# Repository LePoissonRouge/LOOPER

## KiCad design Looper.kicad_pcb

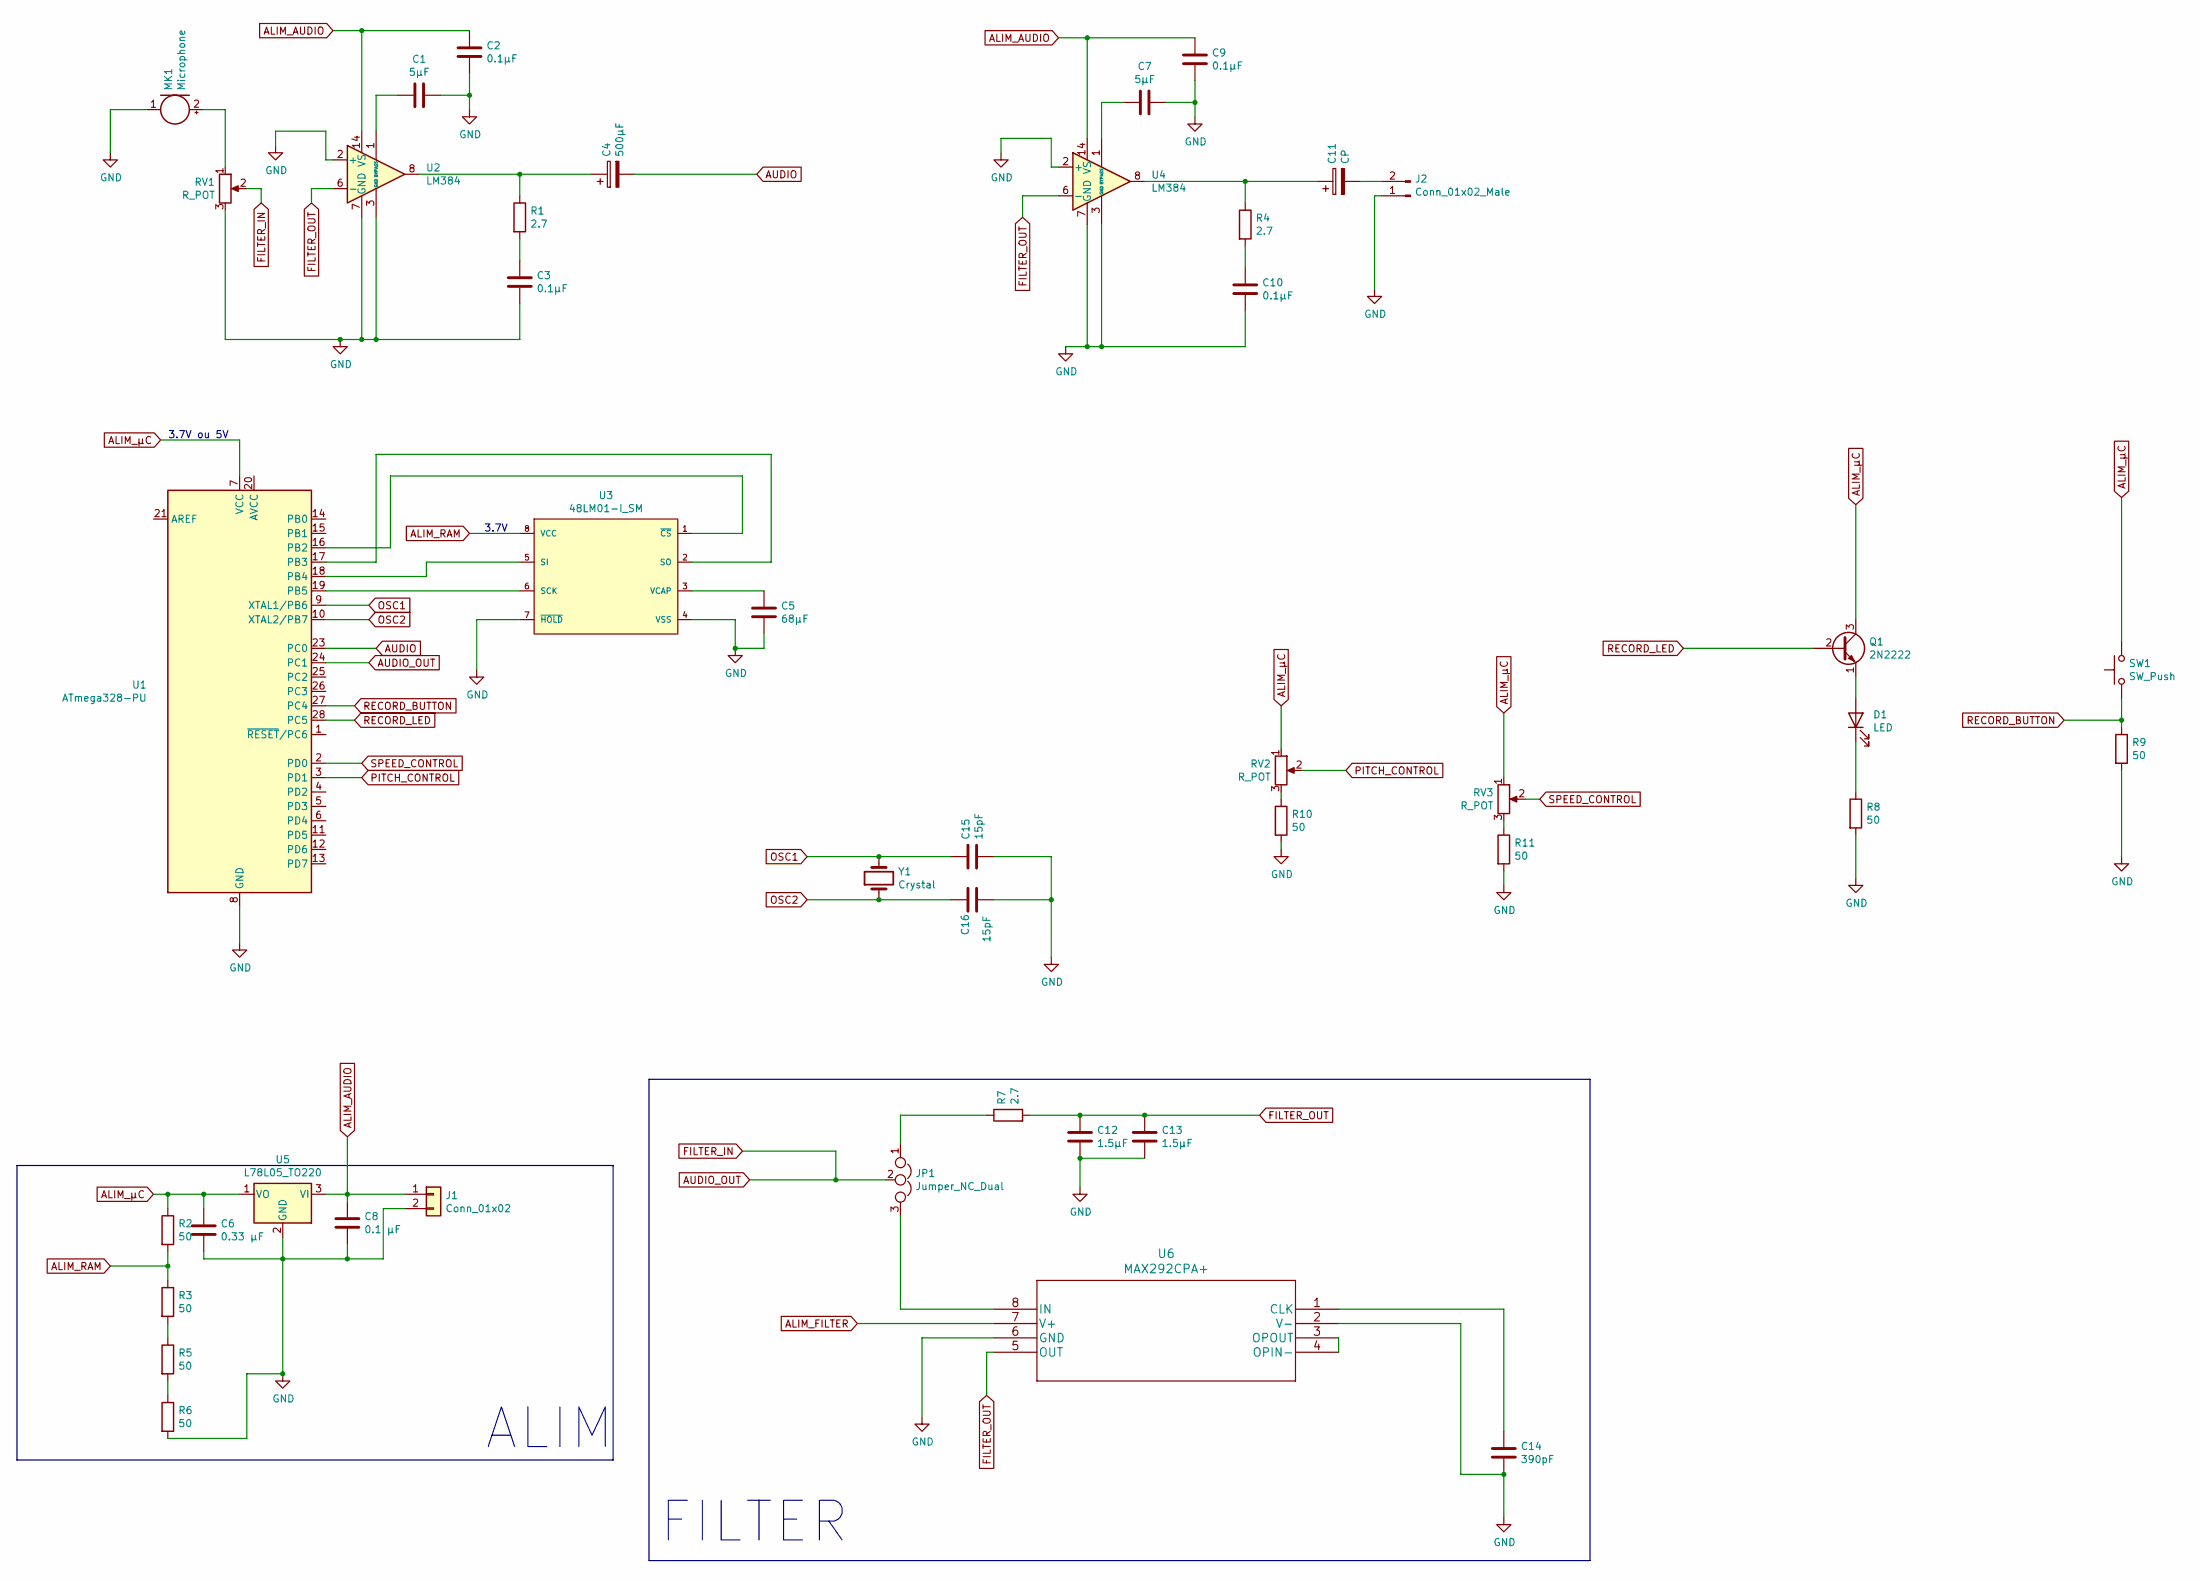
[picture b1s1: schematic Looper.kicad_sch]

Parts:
C1, C7: 5µF; C_Disc_D10.5mm_W5.0mm_P7.50mm
C2, C3, C9, C10: 0.1µF; C_Disc_D10.5mm_W5.0mm_P7.50mm
C4: 500µF; CP_Radial_D8.0mm_P3.50mm
C5: 68µF; C_1206_3216Metric_Pad1.33x1.80mm_HandSolder
C6: 0.33 µF; C_Disc_D10.5mm_W5.0mm_P7.50mm
C8: 0.1 µF; C_Disc_D10.5mm_W5.0mm_P7.50mm
C11: CP; CP_Radial_D8.0mm_P3.50mm
C12, C13: 1.5µF; C_1812_4532Metric_Pad1.57x3.40mm_HandSolder
C14: 390pF; C_Disc_D10.5mm_W5.0mm_P7.50mm
C15, C16: 15pF; C_Disc_D10.5mm_W5.0mm_P7.50mm
D1: LED; LED_D5.0mm
J1: Conn_01x02; TerminalBlock_Phoenix_MKDS-1,5-2-5.08_1x02_P5.08mm_Horizont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
J2: Conn_01x02_Male; TerminalBlock_Phoenix_MKDS-1,5-2-5.08_1x02_P5.08mm_Horizont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
JP1: Jumper_NC_Dual; PinHeader_1x03_P2.54mm_Vertical
MK1: Microphone; R_Axial_DIN0204_L3.6mm_D1.6mm_P1.90mm_Vertical
Q1: 2N2222; TO-18-3
R1, R4, R7: 2.7; R_Axial_DIN0309_L9.0mm_D3.2mm_P12.70mm_Horizontal
R2, R3, R5, R6, R8, R9, R10, R11: 50; R_Axial_DIN0309_L9.0mm_D3.2mm_P12.70mm_Horizontal
RV1, RV2, RV3: R_POT; Potentiometer_Bourns_PTV09A-1_Single_Vertical
SW1: SW_Push; SW_PUSH_6mm
U1: ATmega328-PU; DIP-28_W7.62mm
U2, U4: LM384; DIP-14_W7.62mm
U3: 48LM01-I_SM; Microchip-C04-056-0-C-IPC_A; mouser part number 579-48LM01-I/SM; digikey description IC EERAM 1MBIT SPI 66MHZ 8SOIJ
U5: L78L05_TO220; TO-220-3_Vertical
U6: MAX292CPA+; DIP-8_W7.62mm_Socket_LongPads
Y1: Crystal; Crystal_HC49-U_Vertical

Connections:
ALIM_AUDIO: C2.1, C8.1, C9.1, J1.1, U2.14 (VS), U4.14 (VS), U5.3 (VI)
ALIM_FILTER: U6.7 (V+)
ALIM_RAM: R2.2, R3.1, U3.8 (VCC)
ALIM_µC: C6.1, Q1.3 (C), R2.1, RV2.1, RV3.1, SW1.2, U1.7 (VCC), U5.1 (VO); also elsewhere on the board
AUDIO: C4.2, U1.23 (PC0)
AUDIO_OUT: JP1.2, RV1.2, U1.24 (PC1)
FILTER_OUT: C12.1, C13.1, R7.2, U2.6 (-), U4.6 (-), U6.5 (OUT)
GND: C1.1, C2.2, C3.2, C5.2, C6.2, C7.1, C8.2, C9.2, C10.2, C12.2, C13.2, C14.2, C15.2, C16.2, J1.2, J2.1, MK1.1 (-), R6.2, R8.2, R9.2, R10.2, R11.2, RV1.3, U1.8 (GND), U1.22 (GND), U2.2 (+), U2.3 (GND), U2.4 (GND), U2.5 (GND), U2.7 (GND), U2.10 (GND), U2.11 (GND), U2.12 (GND), U3.4 (VSS), U3.7 (~HOLD), U4.2 (+), U4.3 (GND), U4.4 (GND), U4.5 (GND), U4.7 (GND), U4.10 (GND), U4.11 (GND), U4.12 (GND), U5.2 (GND), U6.2 (V-), U6.6 (GND)
unnamed: C1.2, U2.1 (BYPASS)
unnamed: C3.1, R1.2
unnamed: C4.1, R1.1, U2.8
unnamed: C5.1, U3.3 (VCAP)
unnamed: C7.2, U4.1 (BYPASS)
unnamed: C10.1, R4.2
unnamed: C11.1, R4.1, U4.8
unnamed: C11.2, J2.2
unnamed: C14.1, U6.1 (CLK)
unnamed: D1.1 (K), R8.1
unnamed: D1.2 (A), Q1.1 (E)
unnamed: JP1.1, R7.1
unnamed: JP1.3, U6.8 (IN)
unnamed: MK1.2 (+), RV1.1
unnamed: R3.2, R5.1
unnamed: R5.2, R6.1
unnamed: R10.1, RV2.3
unnamed: R11.1, RV3.3
unnamed: U1.16 (PB2), U3.1 (~CS)
unnamed: U1.17 (PB3), U3.2 (SO)
unnamed: U1.18 (PB4), U3.5 (SI)
unnamed: U1.19 (PB5), U3.6 (SCK)
unnamed: U6.3 (OPOUT), U6.4 (OPIN-)
OSC1: C15.1, U1.9 (XTAL1/PB6), Y1.2
OSC2: C16.1, U1.10 (XTAL2/PB7), Y1.1
PITCH_CONTROL: RV2.2, U1.3 (PD1)
RECORD_BUTTON: R9.1, SW1.1, U1.27 (PC4); also elsewhere on the board
RECORD_LED: Q1.2 (B), U1.28 (PC5)
SPEED_CONTROL: RV3.2, U1.2 (PD0)

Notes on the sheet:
3.7V
ALIM
FILTER
3.7V ou 5V

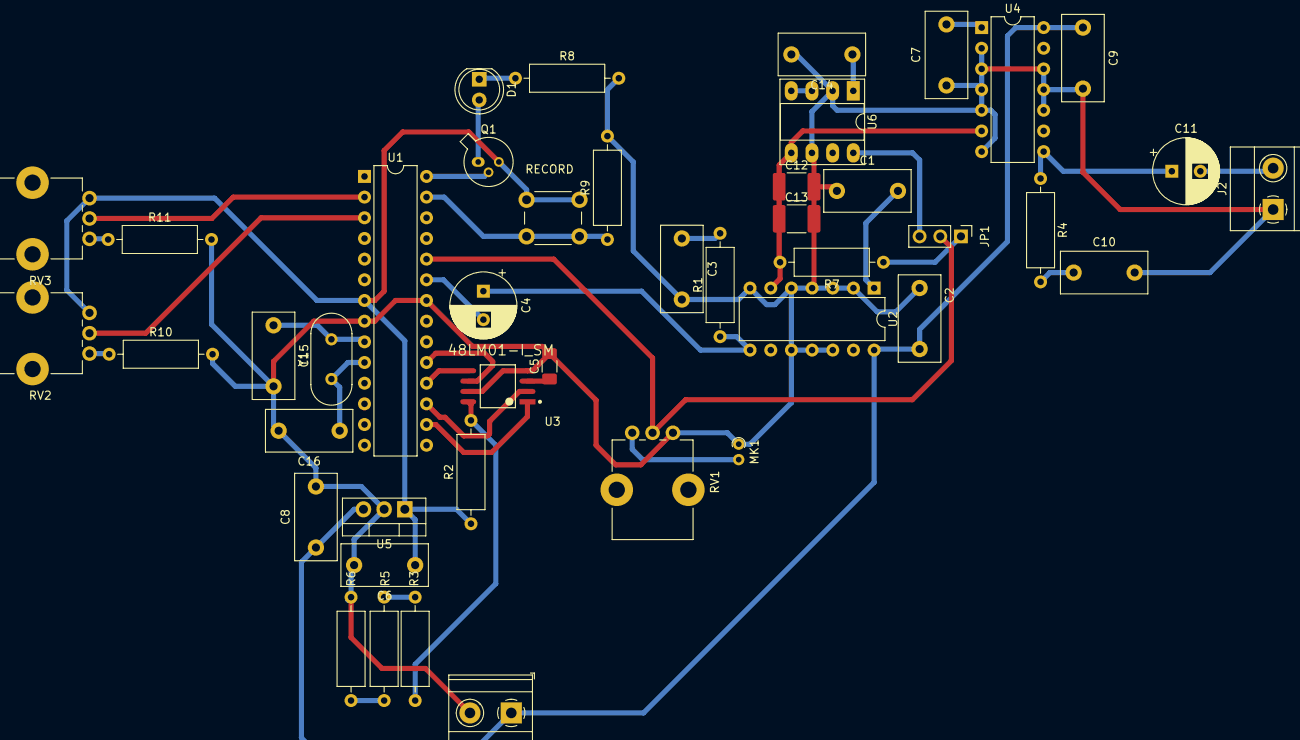
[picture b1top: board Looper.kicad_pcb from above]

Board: 2 copper layers, 44 parts (0 on the bottom side), 36 nets.

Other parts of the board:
RECORD: SW_Push; SW_PUSH_6mm

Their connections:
ALIM_µC: RECORD.2; also elsewhere on the board
RECORD_BUTTON: RECORD.1; also elsewhere on the board
